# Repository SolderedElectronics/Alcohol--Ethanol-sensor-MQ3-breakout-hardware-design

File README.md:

# Alcohol, Ethanol sensor MQ3 breakout Hardware Design

## About the Product

|  |
| :----------------------------------------------------------: |
| [Buy Alcohol, Ethanol sensor MQ3 breakout](https://www.solde.red/333103) |

MQ sensors, including the MQ3 sensor, have the ability to detect various gases. The MQ3 sensor is specifically designed to detect alcohol vapors. This means it is sensitive to alcohols such as methanol, ethanol, and isopropanol. The MQ3 sensor is commonly used to measure the concentration of alcohol in the air and is a useful tool for alerting to the presence of alcohol in the surrounding environment.

It is important to note that MQ sensors are not specific to only one gas and can react to other gases besides those they are specifically designed for. Therefore, it is important to use the MQ3 sensor exclusively for alcohol detection and to follow the manufacturer’s instructions to achieve optimal accuracy and reliability of measurements. It requires a short heating time to function correctly.

The breakout board works with both digital (DO) and analog signals (AO). The digital output is obtained by setting a threshold value with a potentiometer. The analog output will differ depending on the intensity of the gas in the sensor’s environment.

---

## Repository Contents

This repository contains all design files for Alcohol, Ethanol sensor MQ3 breakout, organized as follows:

- **`CAD` folder**: Contains KiCAD design files, including:
  - Schematics
  - PCB layout
  - Panel PCB layout
  - Source 3D files in Fusion360, if any
  - All files are sorted by version with a detailed change log.
- **`OUTPUTS` folder**: Includes all production-ready files, such as:
  - Bill of Materials (BOM) and interactive BOM (iBOM)
  - PDF versions of schematics
  - 3D `.step` file of the board
  - 3D-printable models
  - Gerber files for PCB manufacturing
  - Image of the pinout of the board
  - Product image
  - Compliance, legal and generic sales documents

Refer to the `Change Log` in the CAD folder for details about updates between versions.

---

## Learn More About the Product

Beyond the repository, explore the following resources:

### Soldered Verify

The **Soldered Verify** system ensures every board you purchase from Soldered is fully functional. It also provides access to exclusive test data for your product. To get started, find the unique Soldered Verify ID on your product's packaging and enter the ID on the [Soldered Verify page](https://soldered.com/verify/) to access test results and additional product details.

### Soldered Community

Soldered Community is your go-to place for technical support. Our engineers track and answer all questions posted there, and it’s a great space for the maker community. Get answers to your questions and solutions for your challenges at [Soldered Community](https://soldered.com/community).

### solde.red

solde.red is an ultimate URL shortener and information hub. Access it by typing solde.red/ followed by your product SKU, e.g., [solde.red/333000](https://solde.red/333000), to find getting-started guides, datasheets, open-source hardware and software files, certifications, images, pinouts, and more. Read more about the shortener [here](https://solde.red/info/).

---

## Contributing

Contributions are welcome! Here’s how you can get involved:

- Submit pull requests to enhance the design or fix issues.
- Report bugs or problems by opening an issue.

We encourage community collaboration to make this product even better.

---

## About Soldered

[Soldered for Makers](https://soldered.com) specializes in designing and manufacturing electronic products tailored for enthusiasts, ranging from hobbyists to professionals. Our portfolio includes electronic boards, sensors, and actuators that are widely utilized in fields such as microelectronics, mechatronics, robotics, programming, and IoT. Every product we offer is designed in-house and built upon open-source hardware and software platforms. Proudly certified and manufactured within the European Union, our catalog likely includes the product you need for your project.

We complement these products with comprehensive tutorials and manuals, product descriptions, schematics, programming codes, and project examples. Our round-the-clock [customer and technical support](https://soldered.com/community) is available for all our products, irrespective of the sales channel. Soldered’s success and services reflect our maker community’s unwavering [trust](https://www.trustpilot.com/review/soldered.com), for which we are deeply grateful. Join our community and create using Soldered products.

---

## License

All Soldered open-source hardware (OSH) is under The TAPR Open Hardware License. Read more in the LICENSE file located in this repository.

**Disclaimer:**

No warranty - all designs in this repository are distributed in the hope that they will be useful, but without any warranty. They are provided "AS IS", therefore without warranty of any kind, either expressed or implied. The entire quality and performance of what you do with the contents of this repository are your responsibility. In no event Soldered Electronics will be liable for your damages, or losses, including any general, special, incidental, or consequential damage arising out of the use or inability to use the contents of this repository. 

---

## Have fun!

Thank you for your support from your fellow makers at Soldered Electronics.

Happy Making!

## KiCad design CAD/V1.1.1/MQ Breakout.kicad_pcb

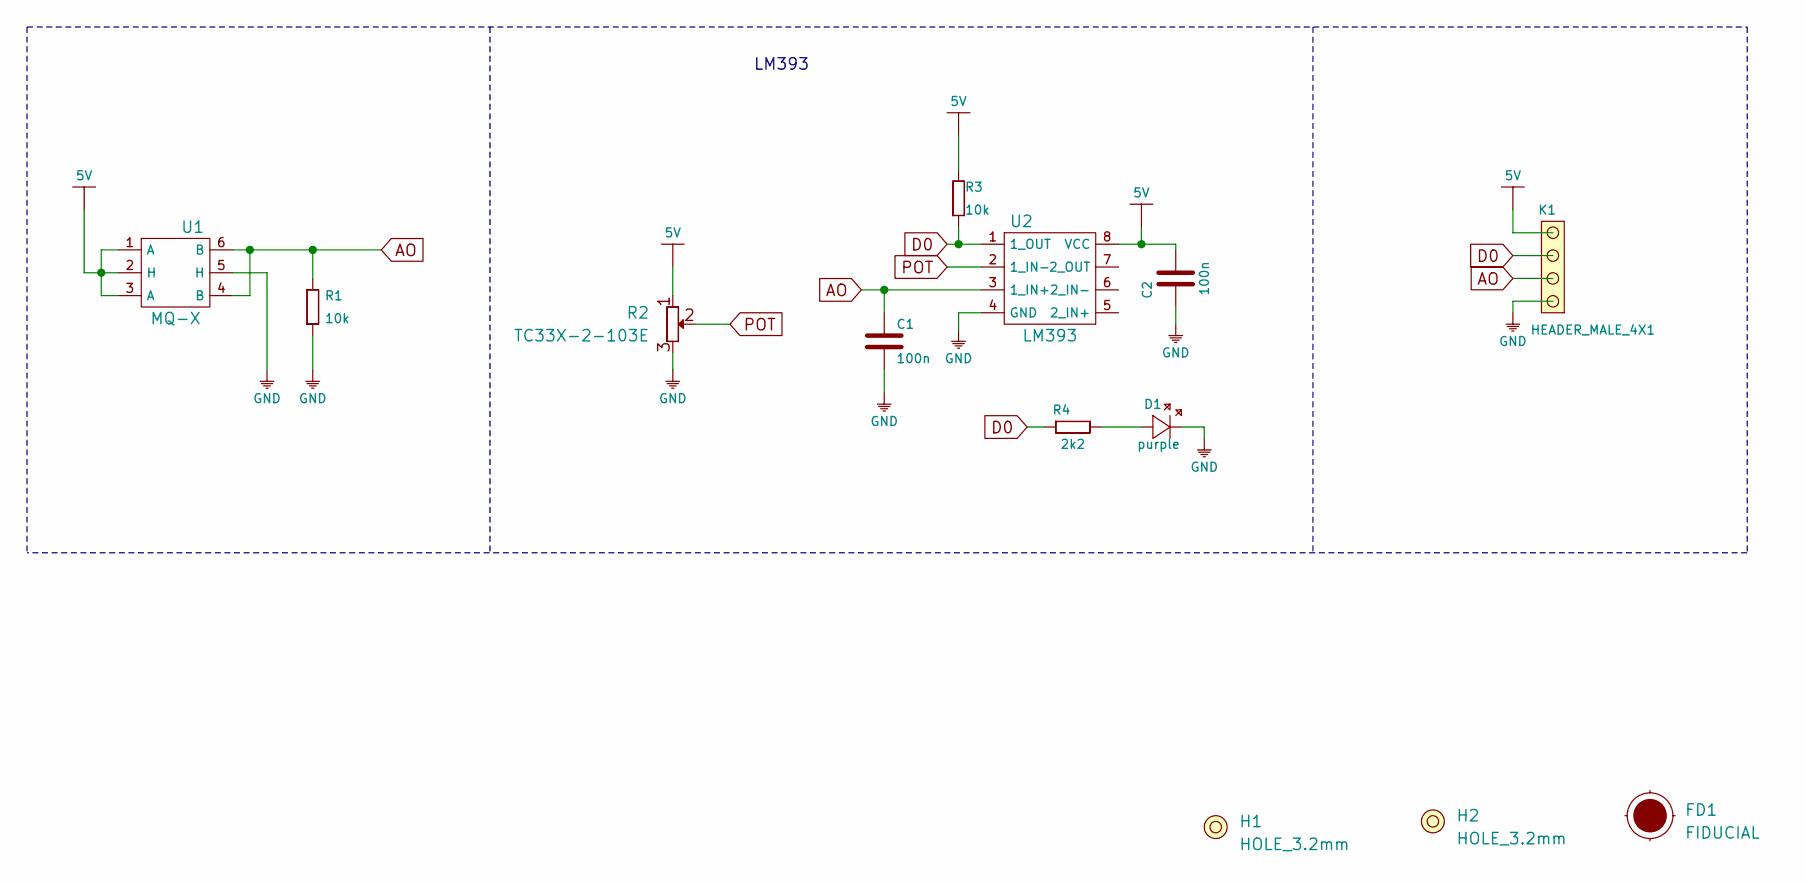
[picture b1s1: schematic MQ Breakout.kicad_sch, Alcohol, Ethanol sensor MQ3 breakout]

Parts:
C1, C2: 100n; 0603C
D1: purple; 0402LED
FD1: FIDUCIAL; FIDUCIAL_23
H1, H2: HOLE_3.2mm
K1: HEADER_MALE_4X1
R1, R3: 10k; 0603R
R2: TC33X-2-103E; tc33x-2-103e
R4: 2k2; 0402R
U1: MQ-X; MQ
U2: LM393; SOIC−8

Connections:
5V: C2.2, K1.4, R2.1, R3.2, U1.1 (A), U1.2 (H), U1.3 (A), U2.8 (VCC)
AO: C1.2, K1.2, R1.2, U1.4 (B), U1.6 (B), U2.3 (1_IN+)
D0: K1.3, R3.1, R4.1, U2.1 (1_OUT)
GND: C1.1, C2.1, D1.2 (K), K1.1, R1.1, R2.3, U1.5 (H), U2.4 (GND)
unnamed: D1.1 (A), R4.2
POT: R2.2, U2.2 (1_IN-)

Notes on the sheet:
LM393

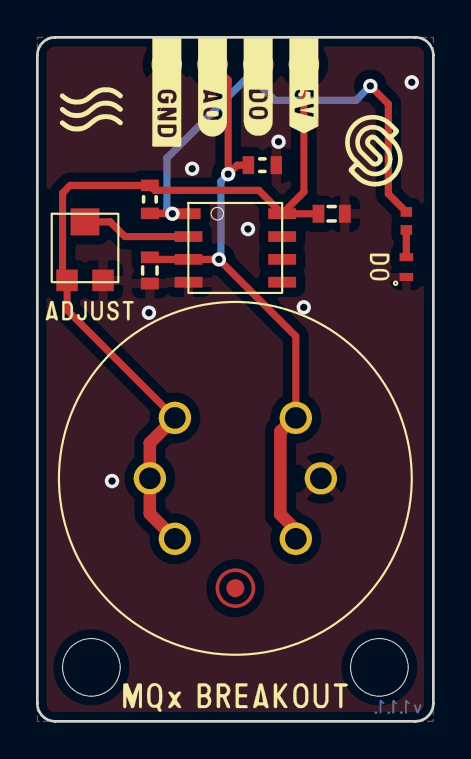
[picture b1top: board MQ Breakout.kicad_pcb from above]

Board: 2 copper layers, 22.0 x 38.0 mm, 13 parts (1 on the bottom side), 6 nets.

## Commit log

2022-08-06 Updating open source files.
